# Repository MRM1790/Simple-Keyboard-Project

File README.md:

# Simple-Keyboard-Project
DIY keyboard from scratch for school projects.
This block diagram displays what parts are considered using in this project. As the following goes, Key switches (Kailh or cherry MX) it is possible to use Choc switches (boxed switches) but for now we are sticking to kailh or cherry mx switches. We are using 3 pin switches for this project. For proof of concept, we have thought about doing a cardboard box with a "WSAD" arrow keys for now. Eventually we will do a full 74 keyboard switches. Microcontroller we plan on using is an Arduino pro micro controller that has a USB C connection for the wire to be connected to the computer or laptop. The goal is to have a keyboard matrix which are key switches that have diodes and wires soldered on each other to create columns and rows to utilize more of the pins that are on the Arduino Pro Microcontroller.  Once that is set up then the user should be able to press a input on the proof of concept model and should display either numbers or letters to the output display monitor.

ATTENTION:
  For the BOM files, designators, and CPL we recommended ordering through JLC PCB since it is configured in their version of excel and ordering process.
  QMK Toolbox will be needed to upload the code in the circuit board which a link will be provided here
  https://qmk.fm/toolbox

ATTENTION: THE SOFTWARE FOR THE KEYBOARD IS LABELED AS BOTH "KEYBOARD.JSON" AND "KEYMAP C" AND THE MAIN THING THAT YOU WILL NEED IS THE FILE THAT SAYS "jam61_default.HEX" then you will plug that into the QMK Toolbox application, and press the reset button on the circuit board in order to flash it. Once you hit the reset button in Toolbox hit flash prompt and the Hex file will go into the circuit.

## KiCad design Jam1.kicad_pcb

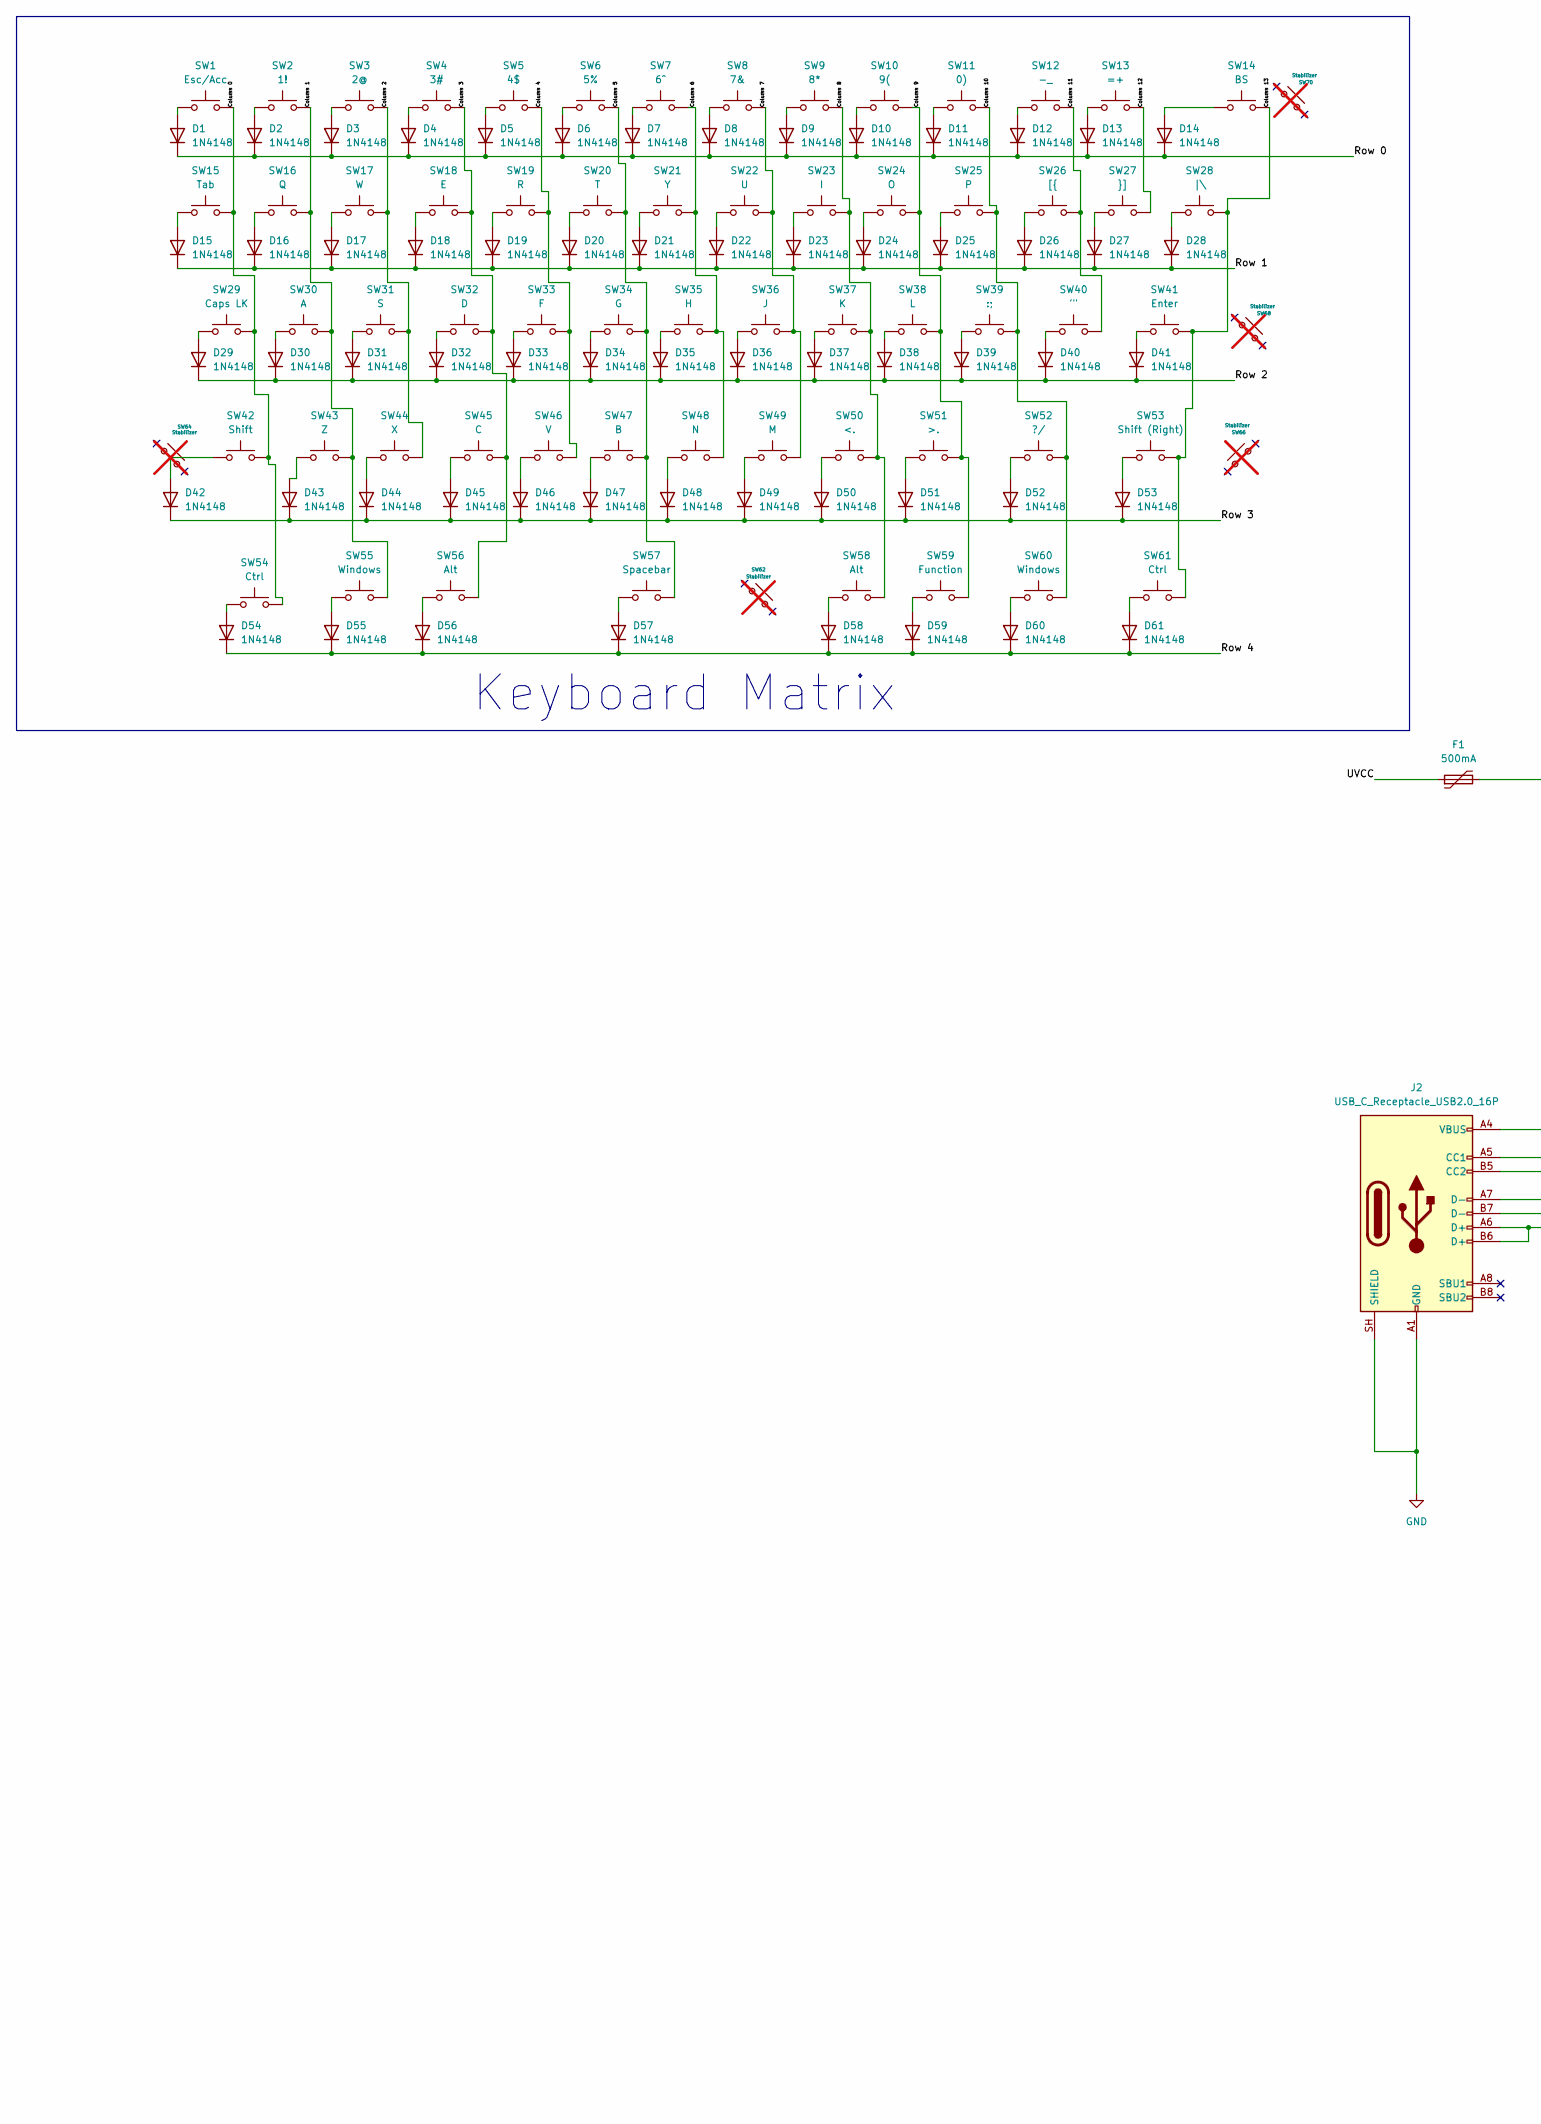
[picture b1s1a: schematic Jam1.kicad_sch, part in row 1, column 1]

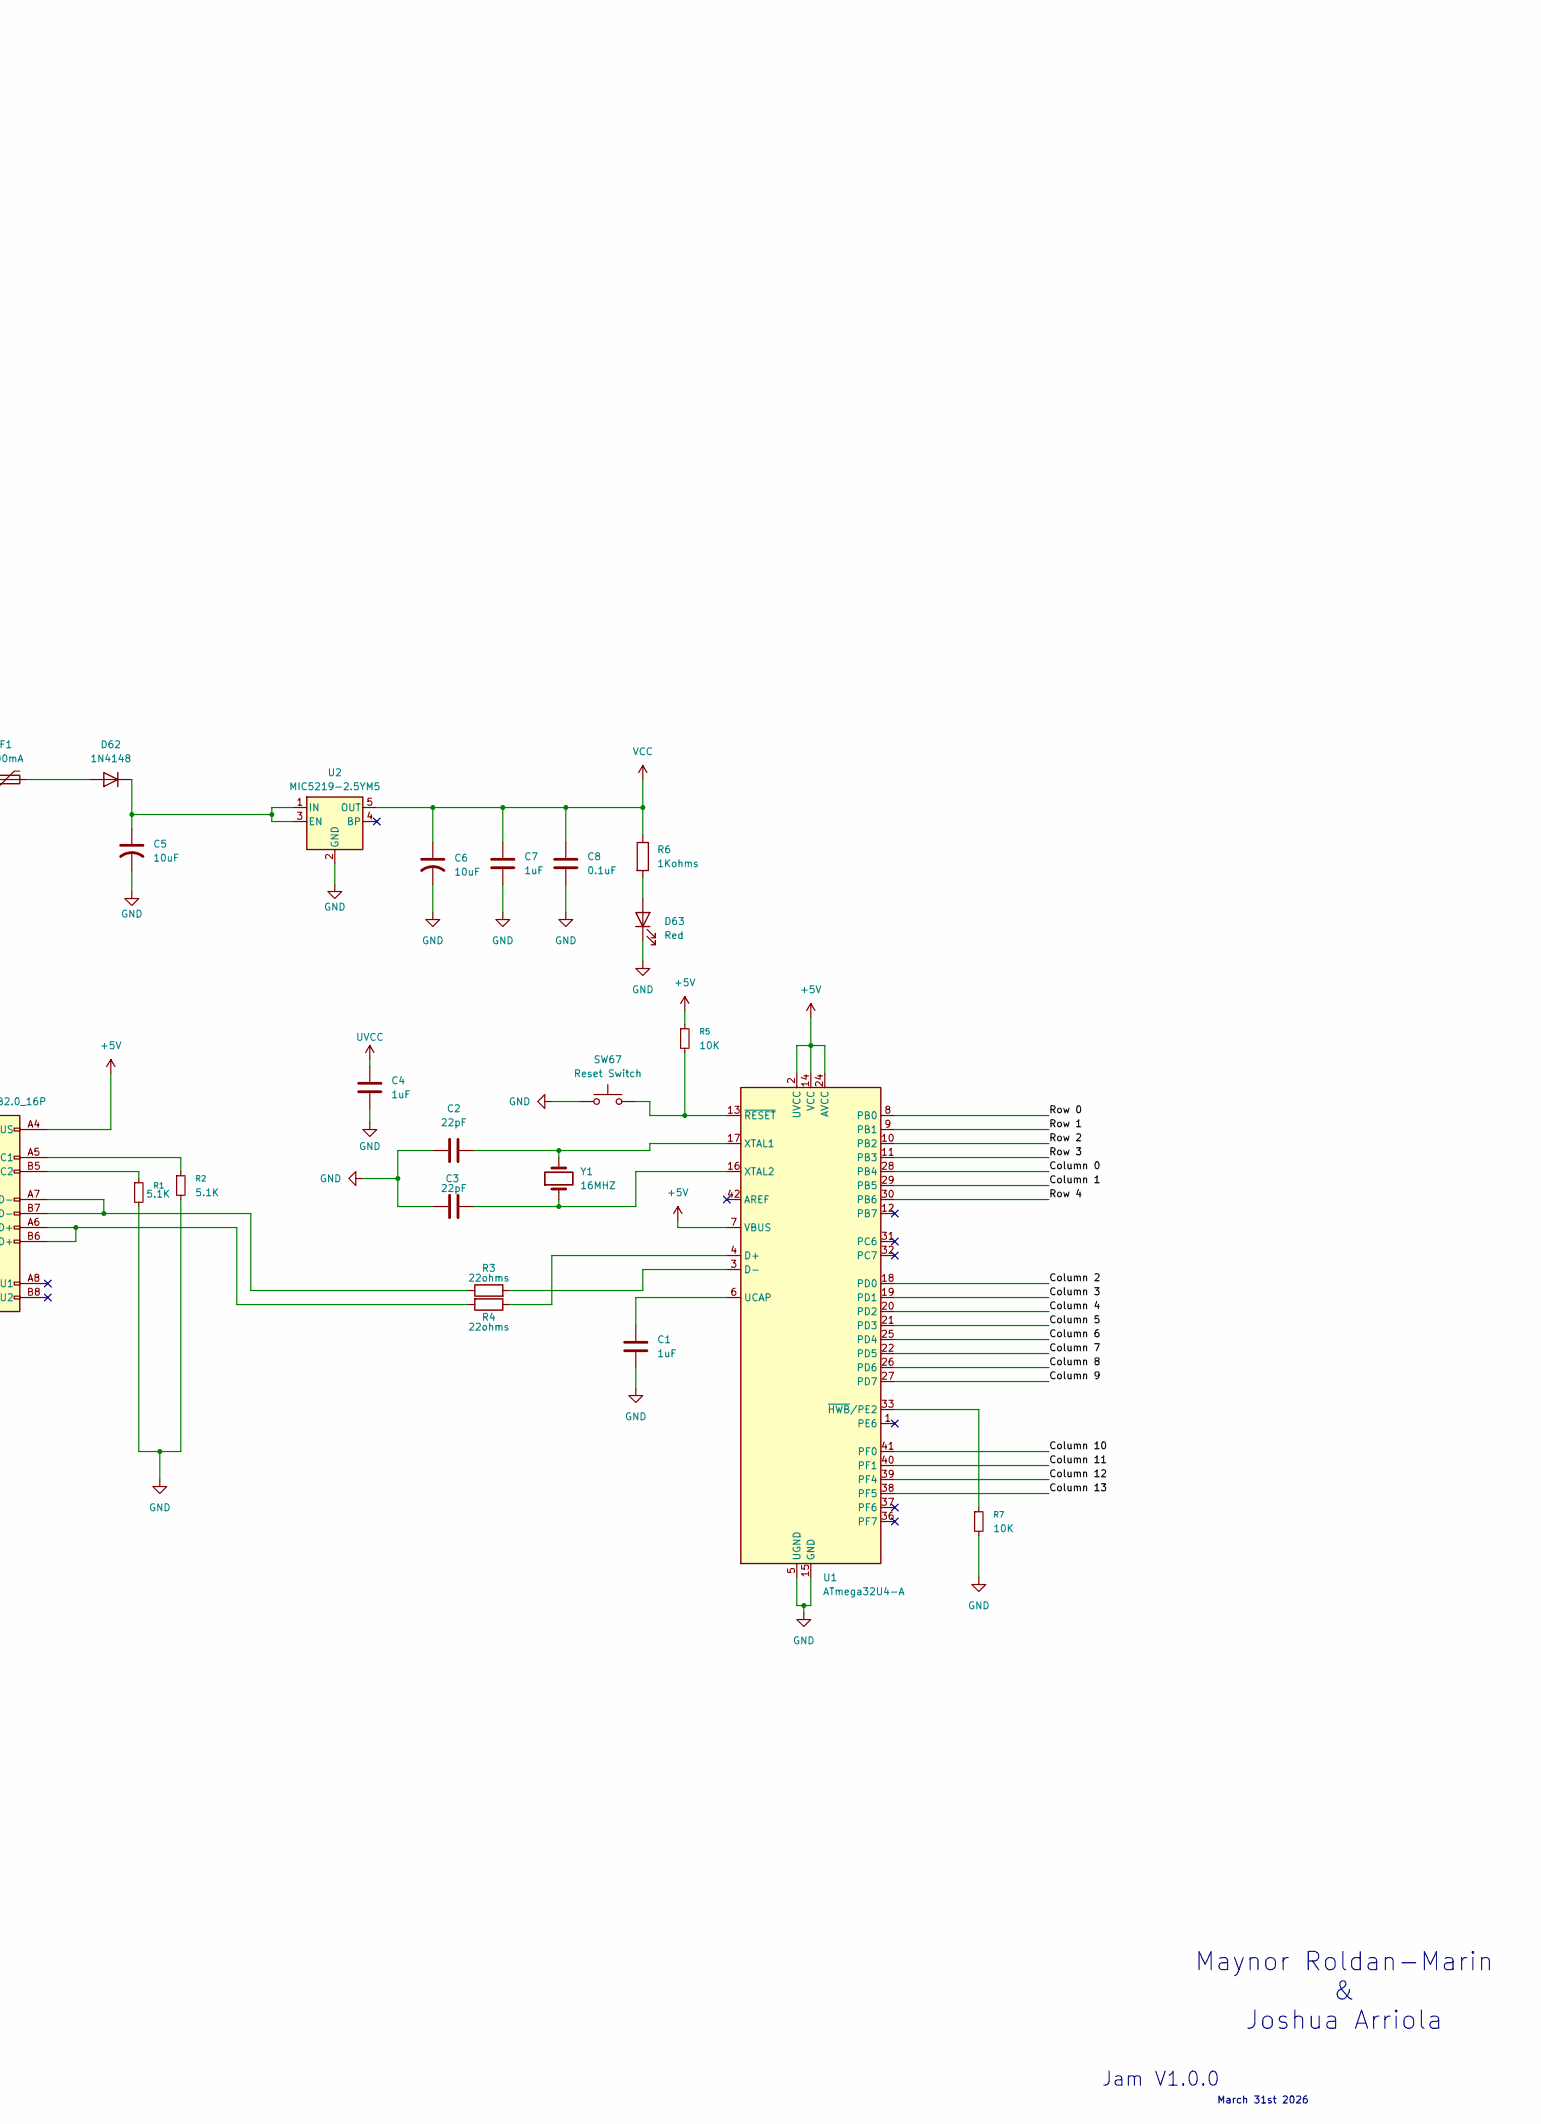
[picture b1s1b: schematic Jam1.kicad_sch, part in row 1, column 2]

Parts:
C1, C4, C7: 1uF; C_0805_2012Metric; LCSC C28323
C2, C3: 22pF; C_0805_2012Metric; LCSC C1804
C5, C6: 10uF; C_0805_2012Metric; LCSC C380332
C8: 0.1uF; C_0805_2012Metric; LCSC C17356222
D1, D2, D3, D4, D5, D6, D7, D8, D9, D10, D11, D12, D13, D14, D15, D16, D17, D18, D19, D20, D21, D22, D23, D24, D25, D26, D27, D28, D29, D30, D31, D32, D33, D34, D35, D36, D37, D38, D39, D40, D41, D42, D43, D44, D45, D46, D47, D48, D49, D50, D51, D52, D53, D54, D55, D56, D57, D58, D59, D60, D61, D62: 1N4148; D_SOD-123; LCSC C2099
D63: Red; LED_0201_0603Metric; LCSC C9900221497
F1: 500mA; Fuse_1206_3216Metric; LCSC C20799
J2: USB_C_Receptacle_USB2.0_16P; USB_C_Receptacle_HRO_TYPE-C-31-M-12; LCSC C2927036
R1, R2: 5.1K; R_0805_2012Metric; LCSC C27834
R3, R4: 22ohms; R_0805_2012Metric; LCSC C3017752
R5, R7: 10K; R_0805_2012Metric; LCSC C17414
R6: 1Kohms; R_0805_2012Metric; LCSC C2889437
SW1: Esc/Acc; Hotswap_MX_Plated_1.00u; LCSC C2803348
SW2: 1!; Hotswap_MX_Plated_1.00u; LCSC C2803348
SW3: 2@; Hotswap_MX_Plated_1.00u; LCSC C2803348
SW4: 3#; Hotswap_MX_Plated_1.00u; LCSC C2803348
SW5: 4$; Hotswap_MX_Plated_1.00u; LCSC C2803348
SW6: 5%; Hotswap_MX_Plated_1.00u; LCSC C2803348
SW7: 6^; Hotswap_MX_Plated_1.00u; LCSC C2803348
SW8: 7&; Hotswap_MX_Plated_1.00u; LCSC C2803348
SW9: 8*; Hotswap_MX_Plated_1.00u; LCSC C2803348
SW10: 9(; Hotswap_MX_Plated_1.00u; LCSC C2803348
SW11: 0); Hotswap_MX_Plated_1.00u; LCSC C2803348
SW12: -_; Hotswap_MX_Plated_1.00u; LCSC C2803348
SW13: =+; Hotswap_MX_Plated_1.00u; LCSC C2803348
SW14: BS; Hotswap_MX_Plated_1.00u; LCSC C2803348
SW15: Tab; Hotswap_MX_Plated_1.00u; LCSC C2803348
SW16: Q; Hotswap_MX_Plated_1.00u; LCSC C2803348
SW17: W; Hotswap_MX_Plated_1.00u; LCSC C2803348
SW18: E; Hotswap_MX_Plated_1.00u; LCSC C2803348
SW19: R; Hotswap_MX_Plated_1.00u; LCSC C2803348
SW20: T; Hotswap_MX_Plated_1.00u; LCSC C2803348
SW21: Y; Hotswap_MX_Plated_1.00u; LCSC C2803348
SW22: U; Hotswap_MX_Plated_1.00u
SW23: I; Hotswap_MX_Plated_1.00u; LCSC C2803348
SW24: O; Hotswap_MX_Plated_1.00u; LCSC C2803348
SW25: P; Hotswap_MX_Plated_1.00u; LCSC C2803348
SW26: [{; Hotswap_MX_Plated_1.00u; LCSC C2803348
SW27: }]; Hotswap_MX_Plated_1.00u; LCSC C2803348
SW28: |\; Hotswap_MX_Plated_1.00u; LCSC C2803348
SW29: Caps LK; Hotswap_MX_Plated_1.00u; LCSC C2803348
SW30: A; Hotswap_MX_Plated_1.00u; LCSC C2803348
SW31: S; Hotswap_MX_Plated_1.00u; LCSC C2803348
SW32: D; Hotswap_MX_Plated_1.00u; LCSC C2803348
SW33: F; Hotswap_MX_Plated_1.00u
SW34: G; Hotswap_MX_Plated_1.00u; LCSC C2803348
SW35: H; Hotswap_MX_Plated_1.00u; LCSC C2803348
SW36: J; Hotswap_MX_Plated_1.00u; LCSC C2803348
SW37: K; Hotswap_MX_Plated_1.00u; LCSC C2803348
SW38: L; Hotswap_MX_Plated_1.00u; LCSC C2803348
SW39: :;; Hotswap_MX_Plated_1.00u; LCSC C2803348
SW40: '"; Hotswap_MX_Plated_1.00u; LCSC C2803348
SW41: Enter; Hotswap_MX_Plated_1.00u; LCSC C2803348
SW42: Shift; Hotswap_MX_Plated_1.00u; LCSC C2803348
SW43: Z; Hotswap_MX_Plated_1.00u; LCSC C2803348
SW44: X; Hotswap_MX_Plated_1.00u; LCSC C2803348
SW45: C; Hotswap_MX_Plated_1.00u; LCSC C2803348
SW46: V; Hotswap_MX_Plated_1.00u; LCSC C2803348
SW47: B; Hotswap_MX_Plated_1.00u; LCSC C2803348
SW48: N; Hotswap_MX_Plated_1.00u; LCSC C2803348
SW49: M; Hotswap_MX_Plated_1.00u; LCSC C2803348
SW50: <.; Hotswap_MX_Plated_1.00u; LCSC C2803348
SW51: >.; Hotswap_MX_Plated_1.00u; LCSC C2803348
SW52: ?/; Hotswap_MX_Plated_1.00u; LCSC C2803348
SW53: Shift (Right); Hotswap_MX_Plated_1.00u; LCSC C2803348
SW54, SW61: Ctrl; Hotswap_MX_Plated_1.00u; LCSC C2803348
SW55, SW60: Windows; Hotswap_MX_Plated_1.00u; LCSC C2803348
SW56, SW58: Alt; Hotswap_MX_Plated_1.00u; LCSC C2803348
SW57: Spacebar; Hotswap_MX_Plated_1.00u; LCSC C2803348
SW59: Function; Hotswap_MX_Plated_1.00u; LCSC C2803348
SW62: Stabilizer; Stabilizer_MX_6.25u; not fitted
SW64, SW66, SW68, SW70: Stabilizer; Stabilizer_MX_2.00u; not fitted
SW67: Reset Switch; SW_SPST_SKQG_WithStem; LCSC C2886894
U1: ATmega32U4-A; TQFP-44_10x10mm_P0.8mm; LCSC C44854
U2: MIC5219-2.5YM5; SOT-23-5; LCSC C18212648
Y1: 16MHZ; Crystal_SMD_3225-4Pin_3.2x2.5mm; LCSC C112972

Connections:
+5V: J2.A4 (VBUS), J2.A9 (VBUS), J2.B4 (VBUS), J2.B9 (VBUS), R5.1, U1.2 (UVCC), U1.7 (VBUS), U1.14 (VCC), U1.24 (AVCC), U1.34 (VCC), U1.44 (AVCC)
/Column 0: SW1.2, SW15.2, SW29.2, SW42.2, SW54.2, U1.28 (PB4)
/Column 1: SW2.2, SW16.2, SW30.2, SW43.2, SW55.2, U1.29 (PB5)
/Column 2: SW3.2, SW17.2, SW31.2, SW44.2, U1.18 (PD0)
/Column 3: SW4.2, SW18.2, SW32.2, SW45.2, SW56.2, U1.19 (PD1)
/Column 4: SW5.2, SW19.2, SW33.2, SW46.2, U1.20 (PD2)
/Column 5: SW6.2, SW20.2, SW34.2, SW47.2, SW57.2, U1.21 (PD3)
/Column 6: SW7.2, SW21.2, SW35.2, SW48.2, U1.25 (PD4)
/Column 7: SW8.2, SW22.2, SW36.2, SW49.2, U1.22 (PD5)
/Column 8: SW9.2, SW23.2, SW37.2, SW50.2, SW58.2, U1.26 (PD6)
/Column 9: SW10.2, SW24.2, SW38.2, SW51.2, SW59.2, U1.27 (PD7)
/Column 10: SW11.2, SW25.2, SW39.2, SW52.2, SW60.2, U1.41 (PF0)
/Column 11: SW12.2, SW26.2, SW40.2, U1.40 (PF1)
/Column 12: SW13.2, SW27.2, U1.39 (PF4)
/Column 13: SW14.2, SW28.2, SW41.2, SW53.2, SW61.2, U1.38 (PF5)
/Row 0: D1.1 (K), D2.1 (K), D3.1 (K), D4.1 (K), D5.1 (K), D6.1 (K), D7.1 (K), D8.1 (K), D9.1 (K), D10.1 (K), D11.1 (K), D12.1 (K), D13.1 (K), D14.1 (K), U1.8 (PB0)
/Row 1: D15.1 (K), D16.1 (K), D17.1 (K), D18.1 (K), D19.1 (K), D20.1 (K), D21.1 (K), D22.1 (K), D23.1 (K), D24.1 (K), D25.1 (K), D26.1 (K), D27.1 (K), D28.1 (K), U1.9 (PB1)
/Row 2: D29.1 (K), D30.1 (K), D31.1 (K), D32.1 (K), D33.1 (K), D34.1 (K), D35.1 (K), D36.1 (K), D37.1 (K), D38.1 (K), D39.1 (K), D40.1 (K), D41.1 (K), U1.10 (PB2)
/Row 3: D42.1 (K), D43.1 (K), D44.1 (K), D45.1 (K), D46.1 (K), D47.1 (K), D48.1 (K), D49.1 (K), D50.1 (K), D51.1 (K), D52.1 (K), D53.1 (K), U1.11 (PB3)
/Row 4: D54.1 (K), D55.1 (K), D56.1 (K), D57.1 (K), D58.1 (K), D59.1 (K), D60.1 (K), D61.1 (K), U1.30 (PB6)
GND: C1.2, C2.1, C3.1, C4.2, C5.2, C6.2, C7.2, C8.2, D63.1 (K), J2.A1 (GND), J2.A12 (GND), J2.B1 (GND), J2.B12 (GND), J2.SH (SHIELD), R1.2, R2.2, R7.2, SW67.1, U1.5 (UGND), U1.15 (GND), U1.23 (GND), U1.35 (GND), U1.43 (GND), U2.2 (GND)
unnamed: D1.2 (A), SW1.1
unnamed: D2.2 (A), SW2.1
unnamed: D3.2 (A), SW3.1
unnamed: D4.2 (A), SW4.1
unnamed: D5.2 (A), SW5.1
unnamed: D6.2 (A), SW6.1
unnamed: D7.2 (A), SW7.1
unnamed: D8.2 (A), SW8.1
unnamed: D9.2 (A), SW9.1
unnamed: D10.2 (A), SW10.1
unnamed: D11.2 (A), SW11.1
unnamed: D12.2 (A), SW12.1
unnamed: D13.2 (A), SW13.1
unnamed: D14.2 (A), SW14.1
unnamed: D15.2 (A), SW15.1
unnamed: D16.2 (A), SW16.1
unnamed: D17.2 (A), SW17.1
unnamed: D18.2 (A), SW18.1
unnamed: D19.2 (A), SW19.1
unnamed: D20.2 (A), SW20.1
unnamed: D21.2 (A), SW21.1
unnamed: D22.2 (A), SW22.1
unnamed: D23.2 (A), SW23.1
unnamed: D24.2 (A), SW24.1
unnamed: D25.2 (A), SW25.1
unnamed: D26.2 (A), SW26.1
unnamed: D27.2 (A), SW27.1
unnamed: D28.2 (A), SW28.1
unnamed: D29.2 (A), SW29.1
unnamed: D30.2 (A), SW30.1
unnamed: D31.2 (A), SW31.1
unnamed: D32.2 (A), SW32.1
unnamed: D33.2 (A), SW33.1
unnamed: D34.2 (A), SW34.1
unnamed: D35.2 (A), SW35.1
unnamed: D36.2 (A), SW36.1
unnamed: D37.2 (A), SW37.1
unnamed: D38.2 (A), SW38.1
unnamed: D39.2 (A), SW39.1
unnamed: D40.2 (A), SW40.1
unnamed: D41.2 (A), SW41.1
unnamed: D42.2 (A), SW42.1
unnamed: D43.2 (A), SW43.1
unnamed: D44.2 (A), SW44.1
unnamed: D45.2 (A), SW45.1
unnamed: D46.2 (A), SW46.1
unnamed: D47.2 (A), SW47.1
unnamed: D48.2 (A), SW48.1
unnamed: D49.2 (A), SW49.1
unnamed: D50.2 (A), SW50.1
unnamed: D51.2 (A), SW51.1
unnamed: D52.2 (A), SW52.1
unnamed: D53.2 (A), SW53.1
unnamed: D54.2 (A), SW54.1
unnamed: D55.2 (A), SW55.1
unnamed: D56.2 (A), SW56.1
unnamed: D57.2 (A), SW57.1
unnamed: D58.2 (A), SW58.1
unnamed: D59.2 (A), SW59.1
unnamed: D60.2 (A), SW60.1
unnamed: D61.2 (A), SW61.1
unnamed: D62.2 (A), F1.2
unnamed: C5.1, D62.1 (K), U2.1 (IN), U2.3 (EN)
unnamed: D63.2 (A), R6.2
unnamed: J2.A5 (CC1), R2.1
unnamed: J2.B5 (CC2), R1.1
unnamed: J2.A6 (D+), J2.B6 (D+), R4.2
unnamed: J2.A7 (D-), J2.B7 (D-), R3.1
unnamed: R4.1, U1.4 (D+)
unnamed: R3.2, U1.3 (D-)
unnamed: C1.1, U1.6 (UCAP)
unnamed: C2.2, U1.17 (XTAL1), Y1.2
unnamed: C3.2, U1.16 (XTAL2), Y1.1
unnamed: R7.1, U1.33 (~HWB/PE2)
unnamed: R5.2, SW67.2, U1.13 (~RESET)
UVCC: C4.1, F1.1
VCC: C6.1, C7.1, C8.1, R6.1, U2.5 (OUT)

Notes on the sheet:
Keyboard Matrix
March 31st 2026
Maynor Roldan-Marin & Joshua Arriola
Jam V1.0.0

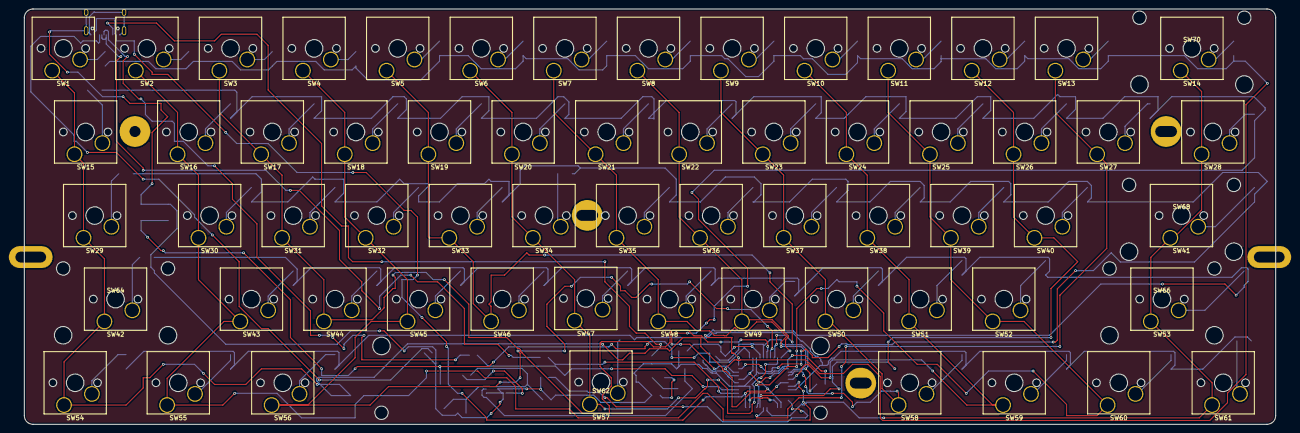
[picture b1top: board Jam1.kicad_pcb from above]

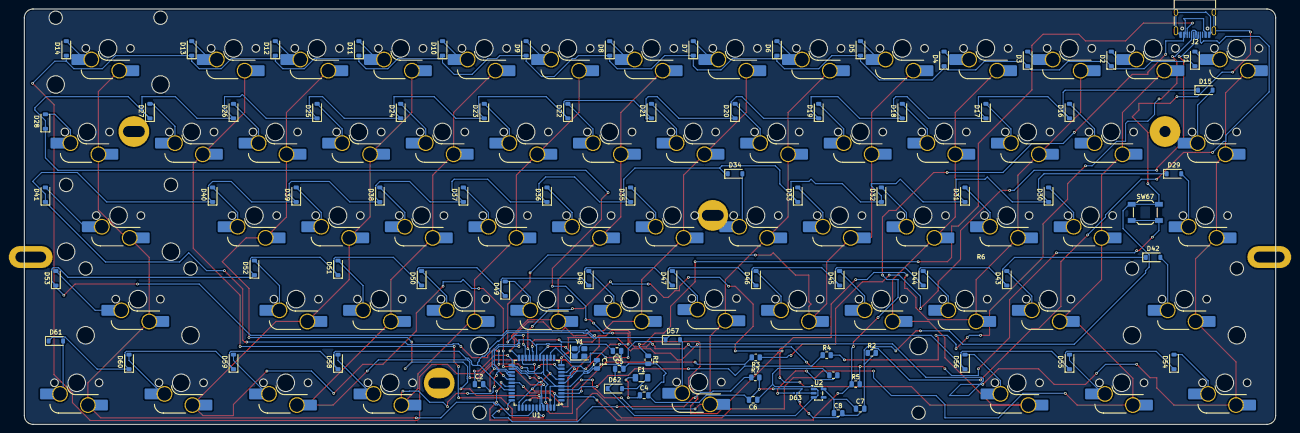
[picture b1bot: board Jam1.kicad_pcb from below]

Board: 2 copper layers, 285.0 x 94.6 mm, 156 parts (84 on the bottom side), 98 nets.

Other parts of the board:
HOLE: VAL**; PKRHSL
HOLE#2: VAL**; PKRHSL
HOLE#3, HOLE#4, HOLE#6: VAL**; PKRH
HOLE#5: VAL**; PKRHC

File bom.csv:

Designator,Footprint,Quantity,Value,LCSC Part #
"C1, C4, C7",805,3,1uF,C28323
"C2, C3",805,2,22pF,C1804
"C5, C6",805,2,10uF,C380332
C8,805,1,0.1uF,C17356222
"D1, D10, D11, D12, D13, D14, D15, D16, D17, D18, D19, D2, D20, D21, D22, D23, D24, D25, D26, D27, D28, D29, D3, D30, D31, D32, D33, D34, D35, D36, D37, D38, D39, D4, D40, D41, D42, D43, D44, D45, D46, D47, D48, D49, D5, D50, D51, D52, D53, D54, D55, D56, D57, D58, D59, D6, D60, D61, D62, D7, D8, D9",D_SOD-123,62,1N4148,C2099
D63,201,1,Red,C9900221497
F1,1206,1,500mA,C20799
J2,USB_C_Receptacle_HRO_TYPE-C-31-M-12,1,USB_C_Receptacle_USB2.0_16P,C2927036
"R1, R2",805,2,5.1K,C27834
"R3, R4",805,2,22ohms,C3017752
"R5, R7",805,2,10K,C17414
R6,805,1,1Kohms,C2889437
SW1,Hotswap_MX_Plated_1.00u,1,Esc/Acc,C2803348
SW10,Hotswap_MX_Plated_1.00u,1,9(,C2803348
SW11,Hotswap_MX_Plated_1.00u,1,0),C2803348
SW12,Hotswap_MX_Plated_1.00u,1,-_,C2803348
SW13,Hotswap_MX_Plated_1.00u,1,=+,C2803348
SW14,Hotswap_MX_Plated_1.00u,1,BS,C2803348
SW15,Hotswap_MX_Plated_1.00u,1,Tab,C2803348
SW16,Hotswap_MX_Plated_1.00u,1,Q,C2803348
SW17,Hotswap_MX_Plated_1.00u,1,W,C2803348
SW18,Hotswap_MX_Plated_1.00u,1,E,C2803348
SW19,Hotswap_MX_Plated_1.00u,1,R,C2803348
SW2,Hotswap_MX_Plated_1.00u,1,1!,C2803348
SW20,Hotswap_MX_Plated_1.00u,1,T,C2803348
SW21,Hotswap_MX_Plated_1.00u,1,Y,C2803348
SW22,Hotswap_MX_Plated_1.00u,1,U,C2803348
SW23,Hotswap_MX_Plated_1.00u,1,I,C2803348
SW24,Hotswap_MX_Plated_1.00u,1,O,C2803348
SW25,Hotswap_MX_Plated_1.00u,1,P,C2803348
SW26,Hotswap_MX_Plated_1.00u,1,[{,C2803348
SW27,Hotswap_MX_Plated_1.00u,1,}],C2803348
SW28,Hotswap_MX_Plated_1.00u,1,|\,C2803348
SW29,Hotswap_MX_Plated_1.00u,1,Caps LK,C2803348
SW3,Hotswap_MX_Plated_1.00u,1,2@,C2803348
SW30,Hotswap_MX_Plated_1.00u,1,A,C2803348
SW31,Hotswap_MX_Plated_1.00u,1,S,C2803348
SW32,Hotswap_MX_Plated_1.00u,1,D,C2803348
SW33,Hotswap_MX_Plated_1.00u,1,F,C2803348
SW34,Hotswap_MX_Plated_1.00u,1,G,C2803348
SW35,Hotswap_MX_Plated_1.00u,1,H,C2803348
SW36,Hotswap_MX_Plated_1.00u,1,J,C2803348
SW37,Hotswap_MX_Plated_1.00u,1,K,C2803348
SW38,Hotswap_MX_Plated_1.00u,1,L,C2803348
SW39,Hotswap_MX_Plated_1.00u,1,:;,C2803348
SW4,Hotswap_MX_Plated_1.00u,1,3#,C2803348
SW40,Hotswap_MX_Plated_1.00u,1,"'""",C2803348
SW41,Hotswap_MX_Plated_1.00u,1,Enter,C2803348
SW42,Hotswap_MX_Plated_1.00u,1,Shift,C2803348
SW43,Hotswap_MX_Plated_1.00u,1,Z,C2803348
SW44,Hotswap_MX_Plated_1.00u,1,X,C2803348
SW45,Hotswap_MX_Plated_1.00u,1,C,C2803348
SW46,Hotswap_MX_Plated_1.00u,1,V,C2803348
SW47,Hotswap_MX_Plated_1.00u,1,B,C2803348
SW48,Hotswap_MX_Plated_1.00u,1,N,C2803348
SW49,Hotswap_MX_Plated_1.00u,1,M,C2803348
SW5,Hotswap_MX_Plated_1.00u,1, $4.00 ,C2803348
SW50,Hotswap_MX_Plated_1.00u,1,<.,C2803348
SW51,Hotswap_MX_Plated_1.00u,1,>.,C2803348
SW52,Hotswap_MX_Plated_1.00u,1,?/,C2803348
SW53,Hotswap_MX_Plated_1.00u,1,Shift (Right),C2803348
"SW54, SW61",Hotswap_MX_Plated_1.00u,2,Ctrl,C2803348
"SW55, SW60",Hotswap_MX_Plated_1.00u,2,Windows,C2803348
"SW56, SW58",Hotswap_MX_Plated_1.00u,2,Alt,C2803348
SW57,Hotswap_MX_Plated_1.00u,1,Spacebar,C2803348
SW59,Hotswap_MX_Plated_1.00u,1,Function,C2803348
SW6,Hotswap_MX_Plated_1.00u,1,5%,C2803348
SW67,SW_SPST_SKQG_WithStem,1,Reset Switch,C2886894
SW7,Hotswap_MX_Plated_1.00u,1,6^,C2803348
SW8,Hotswap_MX_Plated_1.00u,1,7&,C2803348
SW9,Hotswap_MX_Plated_1.00u,1,8*,C2803348
U1,TQFP-44_10x10mm_P0.8mm,1,ATmega32U4-A,C44854
U2,SOT-23-5,1,MIC5219-2.5YM5,C18212648
Y1,Crystal_SMD_3225-4Pin_3.2x2.5mm,1,16MHZ,C112972

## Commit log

2026-02-10 Create Block Diagram Design
    This block diagram displays what parts are considered using in this project. As the following goes, Key switches (Kailh or cherry MX) it is possible to use Choc switches (boxed switches) but for now 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
2026-02-10 Block Diagram Design
    This document displays what parts are being used for this project.
2026-02-10 Adding LogBook of where we are currently progress
    This log book is still a work in progress, and there are still edit to be made in the future, this contains Proof of Concept phase and the soon to be Prototype-like-Phase
2026-02-11 To do tasks (updated Feb 2026)
    This discusses the main plot points of this project and what needs to be focused on and future plans to make the creation come to life.
2026-02-11 Project Definition: JAM (Feb 2026)
    This is a document explaining the main concerns and the project definition that are considered for this project, edits may be possible in the future!
2026-05-14 Added both the matrix coding and remap coding
    These are the codes and mapping for our keyboard project, please not that as of now 55 keys work on the keyboard currently, we are still trying to get the other 6 keys to work with our circuit board
2026-05-14 3D Board Rendering Photo
    3D board rendering model of the top panel and bottom panel.
2026-05-14 Updated Project Definitions and reflection
    Document about our project definitions, what changed, and what we learned as we were creating the project. What needed to be changed, and what we kept along with our progress.
2026-05-14 Design choices and component choices
    Our designs on how to go about designing our projects, after having meetings to discuss and taking notes on how we should design our keyboard to look like. Along with what ideas we had, which ideas w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
2026-05-14 UPDATED Logbook to keep track of changes
    This logbook kept track of our design journey, along with decisions we both had to settle on, what worked, and what did not work. We communicated with each other to discuss what parts needed to be al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
2026-05-14 Jam61 files
    Includes all Gerber files, BOM files, Designators (manufacturer parts), Drill holes, PCB editor, and schematic, and includes all layers used in PCB editor mode
2026-05-14 Schematic PDF plot
    This file contains the schematic PDF version, there is also the actual schematic in the repository.
2026-05-14 User Documentation
    The documents discuss what is relevant for the user to know how to use our circuit board if they plan on getting it developed by a PCB manufacturing company and describes what this circuit is capable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
2026-05-14 Testing Documents
    Discuss different ways we test our project out physically and soft ware wise, it also discuss how to go about testing the hot swappable sockets by either inserting the key switches or using conductiv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
2026-05-14 THIS THE SOFTWARE REQUIRED TO MAP THE KEYBOARD
    This the main code you will need in order to get the circuit board working, grab this file only and use the QMK Toolbox application to upload the software into the circuit. Refer back to the user doc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
2026-05-15 Update on keyboard coding
    As of now only 54 out of the 61 keys are functioning, for some reason one of the columns is acting as if it's dead it may have to do with the way it was mapped on the matrix in kicad
2026-05-15 UPDATED Logbook to keep track of changes
    This logbook kept track of our design journey, along with decisions we both had to settle on, what worked, and what did not work. We communicated with each other to discuss what parts needed to be al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
